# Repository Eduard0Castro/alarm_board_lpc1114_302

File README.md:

# ALARM BOARD LPC1114/302

This repository contains the firmware and validation artefacts for **ALARM_BOARD_LPC1114_302**, developed within the course **PBLE02 – Board Bring-Up and Validation of Electronic Prototypes**, offered by **IESTI – Institute of Systems Engineering and Information Technology** at **UNIFEI – Federal University of Itajubá**, taught by **Prof. Dr. Rodrigo Maximiano Antunes de Almeida**.

The main goal of this work is the bring-up and functional validation of a **printed circuit board (PCB)** designed by students in **PBLE01 (2022)**. In practical terms, the project verifies that the board’s key hardware blocks are operational (clocks, GPIO, UART, I²C, ADC, RTC, LCD and LEDs) and that they can be integrated into a coherent application built around a clear and testable architecture.

The firmware was developed using **MCUXpresso IDE**, with CMSIS headers and direct register-level access for the LPC11xx family, supported by the official microcontroller documentation (e.g., **UM10398**).

<div align="center">

</div>

---

## System overview

The application is organised into small modules to keep the code readable during validation and to allow isolated testing. The board behaves as an interactive LCD-driven system, controlled by push buttons and also by UART commands, continuously sampling an ADC channel and enforcing a simple alarm-by-range mechanism. When the ADC value exits the configured range, the firmware temporarily enters a warning mode and provides a clear visual indication.

Hardware and firmware blocks exercised by this project include:

- GPIO and push buttons for user interaction, including a debouncing strategy.
- LCD 16x2 in 4-bit mode as the user interface for menus and values.
- UART for event injection and parameter configuration through a lightweight protocol.
- I²C and an external RTC for reading/writing time and date.
- ADC for analogue acquisition (a potentiometer is used as a sensor surrogate in the demo).
- LEDs for visual feedback during normal operation and warning signalling.

---

## Firmware features

### LCD menu interface
The LCD acts as the main interface. Each state maps to a screen with a fixed title (top row) and a data/values area (bottom row). The system keeps state-specific behaviour inside dedicated handler functions so changes remain local and the overall flow remains predictable.

### Buttons and event layer
The push buttons (UP, DOWN, LEFT, RIGHT and ENTER/SELECT) generate events for navigation and parameter adjustment. In addition to GPIO, the project accepts UART inputs so you can drive the interface and configure values without relying only on local hardware actions.

A key design point is that the state machine consumes a single event stream: the state logic does not need to know whether an event came from a button or from serial; it only reacts to the event code.

### UART protocol support
Besides single-character navigation commands, the firmware supports a simple delimited message mode to push values (for example, to set thresholds or inject time/date data). This is particularly useful during board validation because you can repeat tests quickly, automate input sequences, and verify that the parsing and application logic are stable.

### ADC monitoring and alarm range checking
The ADC is read continuously in the main loop. The user configures two thresholds:

- Alarm Low (lower bound)
- Alarm High (upper bound)

If the ADC value goes outside the configured range, the system switches to a warning state and enables a clear LED/LCD indication. Once the ADC value returns within the valid range, the firmware automatically returns to the previous state.

### RTC over I²C
Time and date are stored in an external RTC accessed via I²C. The firmware supports reading time/date for display and writing updated values when the user confirms configuration. BCD formatting is used where appropriate, matching the RTC register format.

---

## Finite State Machine (FSM)

The firmware is controlled by a finite state machine where each state corresponds to a specific screen and responsibility. The goal is to keep behaviour isolated: instead of a large loop with many branches, each mode is handled by its own routine, interpreting only the events that make sense for that state.

The main navigation occurs through ENTER, which advances to the next screen. LEFT/RIGHT/UP/DOWN adjust parameters depending on the active state. Independently, the ADC warning condition is evaluated continuously; if an alarm condition is detected, the system enters WARNING and later returns automatically when the ADC value is back within range.

Important note about STATE_TIME_VAR: the symbol exists in the state definitions (legacy/experimental), but it is not used in the final project flow and is intentionally omitted from the menu navigation and from the FSM diagram below.

### States used in this project

- STATE_ALARM: configuration of alarm thresholds (low/high).
- STATE_LANGUAGE: language selection.
- STATE_HOUR / STATE_MINUTE / STATE_SECOND: time configuration steps.
- STATE_TIME: current time display (RTC).
- STATE_DAY / STATE_MONTH / STATE_YEAR: date configuration steps.
- STATE_DATE: current date display (RTC).
- STATE_WARNING: alarm indication when ADC value is out of range.

### High-level state flowchart

The diagram below shows the intended menu flow and the global warning preemption logic.

```mermaid
flowchart TD
    A[STATE_ALARM] -->|ENTER| C[STATE_LANGUAGE]
    C -->|ENTER| D[STATE_HOUR]
    D -->|ENTER| E[STATE_MINUTE]
    E -->|ENTER| F[STATE_SECOND]
    F -->|ENTER| G[STATE_TIME]
    G -->|ENTER| H[STATE_DAY]
    H -->|ENTER| I[STATE_MONTH]
    I -->|ENTER| J[STATE_YEAR]
    J -->|ENTER| K[STATE_DATE]
    K -->|ENTER| A

    W[STATE_WARNING] -->|ADC back in range| R[Return to previous state]

    A -. ADC out of range .-> W
    C -. ADC out of range .-> W
    D -. ADC out of range .-> W
    E -. ADC out of range .-> W
    F -. ADC out of range .-> W
    G -. ADC out of range .-> W
    H -. ADC out of range .-> W
    I -. ADC out of range .-> W
    J -. ADC out of range .-> W
    K -. ADC out of range .-> W
```

---

## Demonstration

<!--

-->

In the demonstration setup, a potentiometer is connected to the ADC input to simulate the behaviour of a sensor. Rotating the potentiometer changes the sampled analogue value and the firmware reacts in real time, allowing you to observe the complete chain: ADC sampling, range comparison, warning signalling and the automatic transition to the WARNING state when the value leaves the configured range.

The demonstration also highlights menu navigation and state transitions, making it easy to see how the FSM coordinates the user interface and how inputs (buttons or UART) trigger state-dependent behaviour.

---

## Build and run (MCUXpresso)

This project was developed and tested with **MCUXpresso IDE**, and that is the recommended workflow to reproduce the same environment used during PBLE02.

Typical steps:

- Import the project into MCUXpresso.
- Ensure CMSIS headers in `required/` are included in the include paths.
- Build in Debug/Release as needed.
- Flash using the available SWD interface and run the firmware on the board.

---

## Kicad Project 

The hardware design for this board is fully documented in KiCad and is stored under docs/kicad/.
This directory contains everything needed to open, inspect, and reproduce the PCB design: the project file, the schematic, and the PCB layout. The intention here is to keep the electrical design and the manufacturing-ready layout versioned together with the firmware, so the validation work can always be traced back to a specific hardware revision.

In practical terms, you will find at `docs/kicad/`:

- The KiCad project file (.kicad_pro), which centralises project settings and links the design files;

- The schematic (.kicad_sch), where the complete circuit is defined and organised by functional blocks;

- The PCB layout (.kicad_pcb), which contains component placement, routing, copper zones, and mechanical constraints used for fabrication.

| Layers view | PCB 3D Layout |
|---|---|
|  |  |

---

## Repository structure

```text
ALARM_BOARD_LPC1114_302/
├─ docs/
│  ├─ kicad/
│  │  ├─ alarm_project.kicad_pcb
│  │  ├─ alarm_project.kicad_pro
│  │  └─ alarm_project.kicad_sch
│  ├─ Guide_LPC111x.pdf
│  ├─ Project Documentation.pdf
│  └─ UM10398.pdf
├─ required/
│  ├─ cmsis_compiler.h
│  ├─ cmsis_gcc.h
│  ├─ cmsis_version.h
│  ├─ core_cm0.h
│  ├─ LPC11xx.h
│  ├─ power_profiles.h
│  └─ system_LPC11xx.h
├─ src/
│  ├─ test/
│  │  ├─ adcMain.c
│  │  ├─ i2cRtcMain.c
│  │  ├─ lcdMain.c
│  │  └─ testLed.c
│  ├─ adc.c
│  ├─ adc.h
│  ├─ clocks.h
│  ├─ event.c
│  ├─ event.h
│  ├─ i2cRtc.c
│  ├─ i2cRtc.h
│  ├─ LCD.c
│  ├─ LCD.h
│  ├─ LED.c
│  ├─ LED.h
│  ├─ main.c
│  ├─ output.c
│  ├─ output.h
│  ├─ peripherics.c
│  ├─ peripherics.h
│  ├─ serial.c
│  ├─ serial.h
│  ├─ stateMachine.c
│  ├─ stateMachine.h
│  ├─ var.c
│  └─ var.h
├─ .gitignore
├─ LICENSE
└─ README.md
```

---

## References

- Almeida, R. M. A. ESM_IHM — Interface Homem-Máquina (IHM) Repository. GitHub repository. Available at: https://github.com/rmaalmeida/ESM_IHM.git

- NXP Semiconductors. UM10398: LPC111x/LPC11Cxx User Manual. (User Manual, LPC11xx family).

- Fernandes, G.; Francisco, A. H. P.; Castro, F. S. Documentação_PBLE01. Project documentation (PBLE01, 2022).

- Rodrigues, R. P. Guide_LPC111x.pdf. Reference material used as baseline for the project. Available in this repository at: `docs/Guide_LPC111x.pdf`

---

## Credits

Authors:

- Eduardo Lenhatti
- Eduardo Castro
- Glauber Moura

**Federal University of Itajubá (UNIFEI) - 2025/2026**

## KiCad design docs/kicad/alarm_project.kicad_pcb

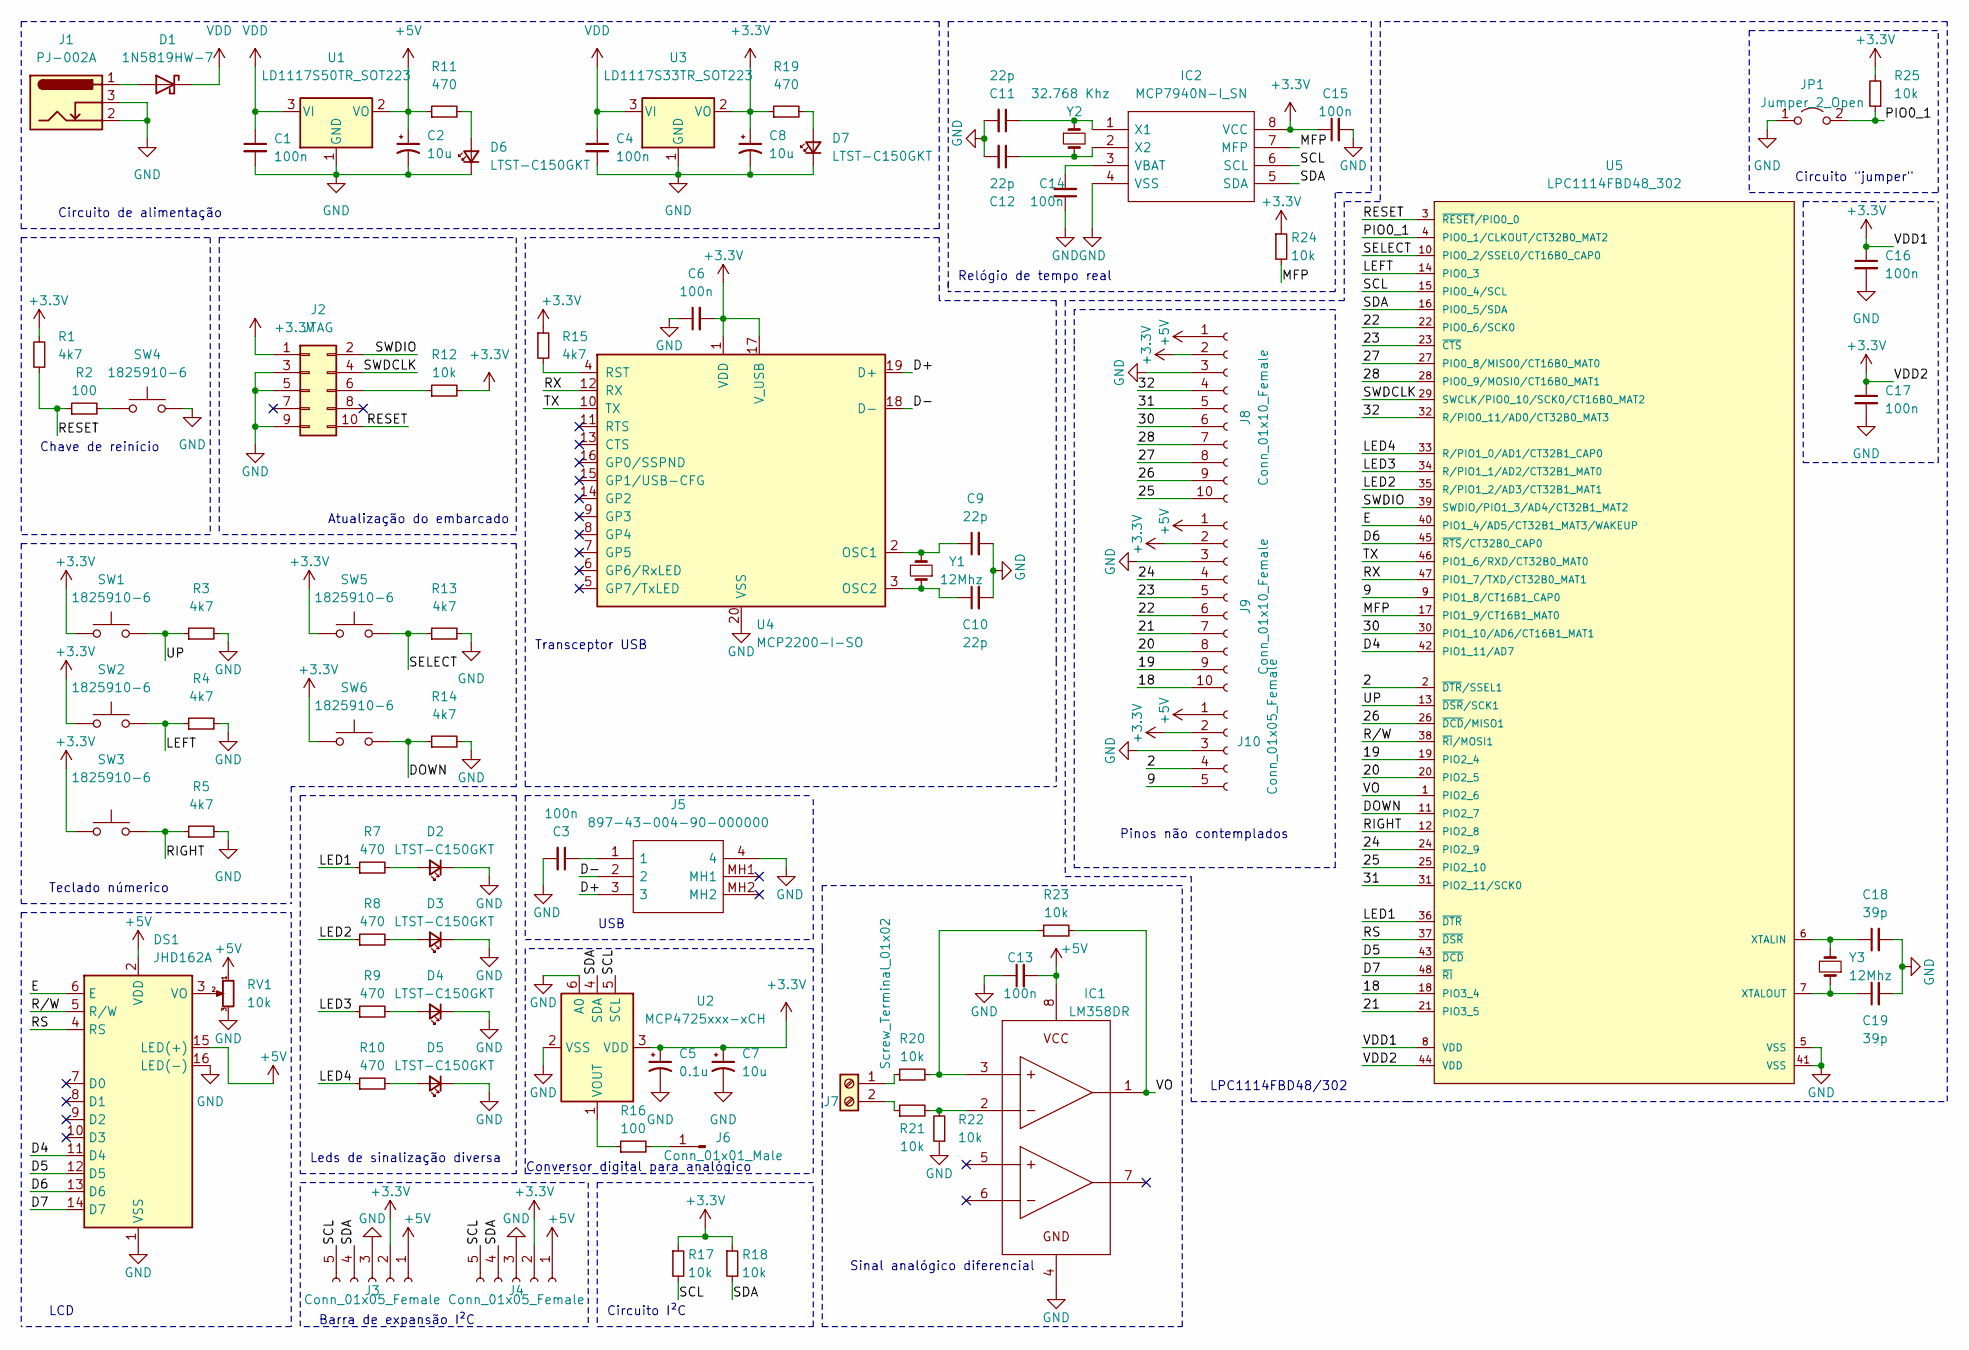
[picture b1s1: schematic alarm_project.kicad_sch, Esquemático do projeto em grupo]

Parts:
C1, C3, C4, C6, C13, C14, C15, C16, C17: 100n; C_0805_2012Metric
C2, C8: 10u; CP_Elec_3x5.3
C5: 0.1u
C7: 10u
C9, C10, C11, C12: 22p; C_0805_2012Metric
C18, C19: 39p; C_0805_2012Metric
D1: 1N5819HW-7; SOD3716X145N
D2, D3, D4, D5, D6, D7: LTST-C150GKT; RESC3015X65
DS1: JHD162A; PinSocket_1x16_P2.54mm_Vertical
IC1: LM358DR; SOIC127P600X175-8N; Manufacturer_Part_Number LM358DR; Mouser Part Number 595-LM358DR
IC2: MCP7940N-I_SN; SOIC127P600X175-8N; Mouser Part Number 579-MCP7940N-I/SN
J1: PJ-002A; CUI_PJ-002A
J2: JTAG; PinHeader_2x05_P2.54mm_Vertical
J3, J4, J10: Conn_01x05_Female; PinSocket_1x05_P2.54mm_Vertical
J5: 897-43-004-90-000000; 8974300490000000; Mouser Part Number 575-8974349
J6: Conn_01x01_Male; PinHeader_1x01_P2.54mm_Vertical
J7: Screw_Terminal_01x02; TerminalBlock_Phoenix_MKDS-1,5-2-5.08_1x02_P5.08mm_Horizont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
J8, J9: Conn_01x10_Female; PinSocket_1x10_P2.54mm_Vertical
JP1: Jumper_2_Open; PinHeader_1x02_P2.54mm_Vertical
R1, R3, R4, R5, R13, R14, R15: 4k7; R_0805_2012Metric
R2, R16: 100; R_0805_2012Metric
R7, R8, R9, R10, R11, R19: 470; R_0805_2012Metric
R12, R17, R18, R20, R21, R22, R23, R24, R25: 10k; R_0805_2012Metric
RV1: 10k; Potentiometer_Bourns_3296W_Vertical
SW1, SW2, SW3, SW4, SW5, SW6: 1825910-6; SW_1825910-6-4
U1: LD1117S50TR_SOT223; SOT-223-3_TabPin2
U2: MCP4725xxx-xCH; SOT-23-6
U3: LD1117S33TR_SOT223; SOT-223-3_TabPin2
U4: MCP2200-I-SO; SOIC-20W_7.5x12.8mm_P1.27mm
U5: LPC1114FBD48_302; NXP_Semiconductors-LPC1114FBD48_302-Manufacturer_Recommended
Y1, Y3: 12Mhz; ATS12A
Y2: 32.768 Khz; AB38T32768KHZ

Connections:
+5V: C2.1, C13.2, DS1.2 (VDD), DS1.15 (LED(+)), IC1.8, J3.1, J4.1, J8.1, J9.1, J10.1, R11.1, RV1.1, U1.2 (VO)
/2: J10.4, U5.2 (~DTR/SSEL1)
/9: J10.5, U5.9 (PIO1_8/CT16B1_CAP0)
/18: J9.10, U5.18 (PIO3_4)
/19: J9.9, U5.19 (PIO2_4)
/20: J9.8, U5.20 (PIO2_5)
/21: J9.7, U5.21 (PIO3_5)
/22: J9.6, U5.22 (PIO0_6/SCK0)
/23: J9.5, U5.23 (~CTS)
/24: J9.4, U5.24 (PIO2_9)
/25: J8.10, U5.25 (PIO2_10)
/26: J8.9, U5.26 (~DCD/MISO1)
/27: J8.8, U5.27 (PIO0_8/MISO0/CT16B0_MAT0)
/28: J8.7, U5.28 (PIO0_9/MOSI0/CT16B0_MAT1)
/30: J8.6, U5.30 (PIO1_10/AD6/CT16B1_MAT1)
/31: J8.5, U5.31 (PIO2_11/SCK0)
/32: J8.4, U5.32 (R/PIO0_11/AD0/CT32B0_MAT3)
/D4: DS1.11 (D4), U5.42 (PIO1_11/AD7)
/D5: DS1.12 (D5), U5.43 (~DCD)
/D6: DS1.13 (D6), U5.45 (~RTS/CT32B0_CAP0)
/D7: DS1.14 (D7), U5.48 (~RI)
/D+: J5.3, U4.19 (D+)
/D-: J5.2, U4.18 (D-)
/E: DS1.6 (E), U5.40 (PIO1_4/AD5/CT32B1_MAT3/WAKEUP)
/LED1: R7.1, U5.36 (~DTR)
/LED2: R8.1, U5.35 (R/PIO1_2/AD3/CT32B1_MAT1)
/LED3: R9.1, U5.34 (R/PIO1_1/AD2/CT32B1_MAT0)
/LED4: R10.1, U5.33 (R/PIO1_0/AD1/CT32B1_CAP0)
/MFP: IC2.7 (MFP), R24.2, U5.17 (PIO1_9/CT16B1_MAT0)
/PIO0_1: JP1.2 (B), R25.1, U5.4 (PIO0_1/CLKOUT/CT32B0_MAT2)
/RESET: J2.10, R1.1, R2.1, U5.3 (~RESET/PIO0_0)
/RS: DS1.4 (RS), U5.37 (~DSR)
/RX: U4.12 (RX), U5.47 (PIO1_7/TXD/CT32B0_MAT1)
/R/W: DS1.5 (R/W), U5.38 (~RI/MOSI1)
/SCL: IC2.6 (SCL), J3.5, J4.5, R17.2, U2.5 (SCL), U5.15 (PIO0_4/SCL)
/SDA: IC2.5 (SDA), J3.4, J4.4, R18.2, U2.4 (SDA), U5.16 (PIO0_5/SDA)
/SELECT: R13.1, SW5.2, U5.10 (PIO0_2/SSEL0/CT16B0_CAP0)
/SWDCLK: J2.4, U5.29 (SWCLK/PIO0_10/SCK0/CT16B0_MAT2)
/SWDIO: J2.2, U5.39 (SWDIO/PIO1_3/AD4/CT32B1_MAT2)
/TX: U4.10 (TX), U5.46 (PIO1_6/RXD/CT32B0_MAT0)
/UP: R3.1, SW1.2, U5.13 (~DSR/SCK1)
/VO: IC1.1, R23.2, U5.1 (PIO2_6)
unnamed: C3.1, J5.1
unnamed: D1.2 (A), J1.1
unnamed: D2.2 (A), R7.2
unnamed: D3.2 (A), R8.2
unnamed: D4.2 (A), R9.2
unnamed: D5.2 (A), R10.2
unnamed: D6.2 (A), R11.2
unnamed: D7.2 (A), R19.2
unnamed: DS1.3 (VO), RV1.2
unnamed: IC1.2, R21.2, R22.2
unnamed: IC1.3, R20.2, R23.1
unnamed: C14.2, IC2.3 (VBAT)
unnamed: C11.1, IC2.1 (X1), Y2.1
unnamed: C12.1, IC2.2 (X2), Y2.2
unnamed: J2.6, R12.1
unnamed: J6.1, R16.2
unnamed: J7.1, R20.1
unnamed: J7.2, R21.1
unnamed: R16.1, U2.1 (VOUT)
unnamed: C9.1, U4.2 (OSC1), Y1.2
unnamed: C10.1, U4.3 (OSC2), Y1.1
unnamed: R15.2, U4.4 (RST)
unnamed: C18.1, U5.6 (XTALIN), Y3.2
unnamed: C19.1, U5.7 (XTALOUT), Y3.1
VDD: C1.1, C4.1, D1.1 (K), U1.3 (VI), U3.3 (VI)

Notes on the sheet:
Conversor digital para analógico
Circuito de alimentação
Circuito "jumper"
Relógio de tempo real
LCD
Teclado númerico
USB
Circuito I²C
Chave de reinício
Leds de sinalização diversa
LPC1114FBD48/302
Transceptor USB
Pinos não contemplados
Barra de expansão I²C
Atualização do embarcado
Sinal analógico diferencial

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
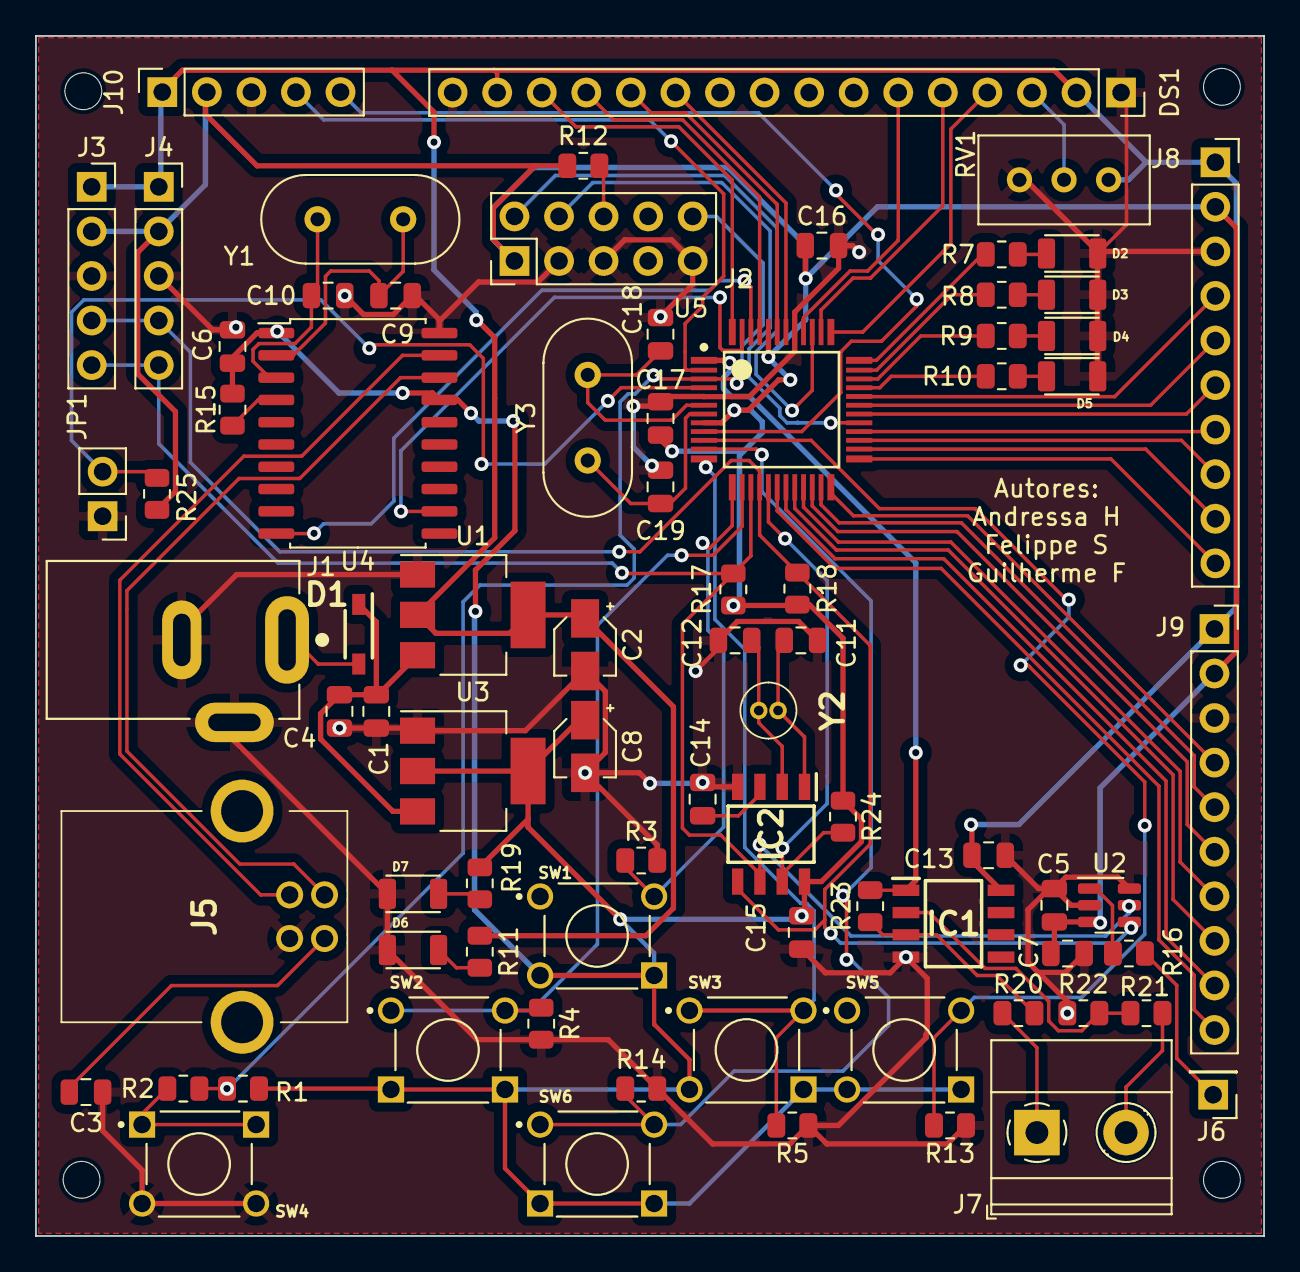
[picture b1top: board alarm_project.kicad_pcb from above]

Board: 2 copper layers, 70.0 x 68.4 mm, 79 parts (0 on the bottom side), 73 nets.

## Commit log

2025-07-08 update: add uart clock support
2025-07-08 feat: add adc read support
2025-07-08 update: add adc clock support
2025-07-08 feat: add main function for adc test
2025-07-08 refactor: test adc using leds and lcd
2025-07-08 update: test adc using leds and lcd
2025-07-10 feat: add adc functions and alarm state to state machine loop
2026-01-30 refactor: optimization of state machine logic and redefinition and standardization of nomenclatures
    reorganization of the repository directory structure
2026-01-30 feat: add README.md, docs, required files and images directories
2026-01-30 add code of conduct
2026-01-30 refactor(img): change images resolution
